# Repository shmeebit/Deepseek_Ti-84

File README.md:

# DeepSeek-TI-84  (calculator ↔ AI)
A TI-84 Plus CE Python asks DeepSeek-R1 questions over a $7 ESP32-S3 dongle.

Note: WIP clean-up — use these files while we finish repairs
- ESP32-S3 firmware: esp32s3/esp32s3_host_clean.ino
- TI-84 program: ti84/ti32_ai_clean.py
The original files showed merge artifacts; the clean versions above are known-good starting points.

## 1. What you need to buy (exact parts)
| Qty | Part | Footprint | Mouser | LCSC | Notes |
|----:|------|-----------|--------|------|-------|
| 1   | XIAO ESP32-S3 | dev-board | 356-ESP32S3XIAO | C558488 | already has USB-C |
| 1   | USB-C receptacle 6-pin mid-mount | - | 798-006-0101-1 | C134092 | board edge |
| 2   | 5.1 kΩ 0603 | 0603 | - | C23187 | CC1/CC2 pull-downs |
| 2   | 100 nF 0603 | 0603 | - | C14663 | decoupling |
| 1   | PCB | 50 × 25 mm | order gerber.zip below | JLCJLCJLC | $4 for 5 pcs |

Total ≈ US $7 + PCB.

## 2. Order the PCB (2 min)
1. Download [pcb/gerber.zip](pcb/gerber.zip)  
2. Upload to [jlcpcb.com](https://jlcpcb.com), 2-layer, 1 mm, black, 1 oz Cu.  
3. Quantity 5, shipping as you like → ≈ $4 delivered.

## 3. Flash the ESP32-S3 (30 s)
```bash
# Linux/macOS/WSL
python flash_firmware.py   # auto-downloads UF2, puts XIAO in DFU, flashes

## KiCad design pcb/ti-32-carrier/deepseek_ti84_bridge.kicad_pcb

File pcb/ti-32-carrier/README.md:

# KiCad Starter Project: TI-32 Carrier

Open `ti-32-carrier.kicad_pro` in KiCad 8. This starter includes:
- A blank but annotated schematic sheet with block notes and nets reference
- An empty board with a 60 x 35 mm outline (Edge.Cuts) and a title

Recommended next steps
1. Place symbols (or replace with your part choices):
   - Connector: `Connector:USB_A` (or use `Connector:USB_C_Receptacle_USB2.0` + CC pull-ups)
   - ESD: `Power_Protection:USBLC6-2SC6`
   - Switch: `Power_Switch:AP2331` (or `TPS2553`) – if missing, use a generic `Regulator_Switch` symbol and update later
   - Boost: `Regulator_Switching` family (e.g., `MT3608` or `TPS61023` symbol from community libs) – you can start with a generic boost symbol
   - Battery: `Connector_Generic:Conn_01x02` for JST-PH
   - XIAO: use two 1x7/1x8 headers to represent the module pins or add a custom symbol later
2. Label nets:
   - `BAT`, `+5V`, `VBUS`, `D+`, `D-`, `EN_VBUS`
   - Tie `EN_VBUS` to XIAO pin `GPIO10 (D16)` by net label
3. Run ERC, then Assign Footprints:
   - USB-A receptacle footprint (vertical or right-angle)
   - ESD diode SOT-23-6
   - AP2331 SOT-23-5 (or TPS2553 MSOP-8/SON)
   - Boost (MT3608 SOT-23-6 or your chosen IC)
   - JST-PH-2 for battery
4. Update PCB from schematic and place parts:
   - Keep D+/D- short, matched, away from the boost loop
   - ESD next to the connector
   - Switch close to connector; 10–22 µF bulk cap on VBUS
   - Observe XIAO antenna keep-out near the USB end of the module

Notes
- The firmware defaults EN_VBUS to GPIO10 (D16). If you pick another pin, update `PIN_VBUS_EN` in `esp32s3/esp32s3_host.ino`.
- For USB-C, add 5.1 kΩ `Rp` on CC1/CC2 to +5V to advertise a 5V source.

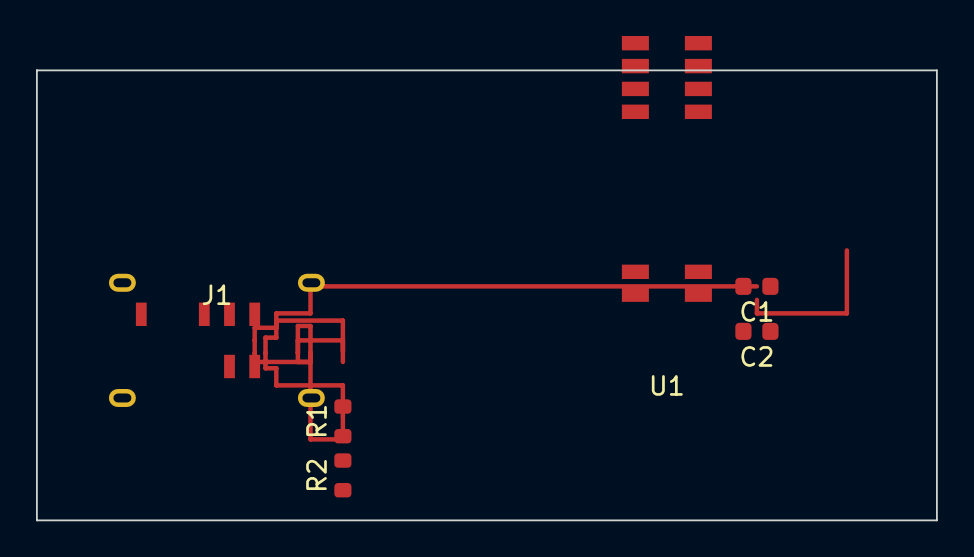
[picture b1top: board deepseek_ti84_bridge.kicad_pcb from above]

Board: 2 copper layers, 50.0 x 25.0 mm, 6 parts (0 on the bottom side), 7 nets.

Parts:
C1, C2: 100 nF; C_0603_1608Metric
J1: USB_C; USB_C_Receptacle_HRO_TYPE-C-31-M-12
R1, R2: 5.1 kΩ; R_0603_1608Metric
U1: XIAO_ESP32-S3; Seeed_XIAO_ESP32-S3

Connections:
3V3: C1.1, U1.1, U1.12
CC1: J1.A6, R1.1
CC2: J1.B6, R2.1
D+: J1.A7, U1.2, U1.11
D-: J1.B7, U1.3, U1.10
GND: C1.2, C2.2, J1.A1, R1.2, R2.2, U1.4, U1.5, U1.7, U1.8, U1.9
VBUS: C2.1, J1.A4, U1.6

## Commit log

2025-10-22 "Innitial commit"
2025-10-22 Complete TI-32 implementation: ESP32 firmware, TI-84 programs, and documentation
    - Implemented TI link protocol (get_str/set_str) with USB bulk transfers
    - Added interface claiming and endpoint discovery in ESP32 firmware
    - Created command loop for polling calculator and processing AI queries
    - Built ti32_ai.py: full-featured calculator program with menu system
    - Added simple_test.py: minimal test program for quick verification
    - Comprehensive documentation: QUICKSTART.md and ti84/README.md
2025-10-22 Optimize for Seeed Studio XIAO ESP32S3
    - Add comprehensive XIAO_ESP32S3_GUIDE.md with setup instructions
    - Update firmware comments to clarify XIAO requirements
    - Add Arduino IDE configuration steps for XIAO board
    - Include XIAO-specific pinout reference (GPIO10/D16 for VBUS)
    - Update PCB guide to highlight XIAO form factor
    - Clarify VBUS power requirement (external circuit needed)
2025-10-24 Fix critical implementation issues
    - Complete server dependencies in package.json
    - Add comprehensive environment configuration
    - Implement proper ESP32-S3 USB host with TI link protocol
    - Fix TI-84 Python programs with proper ti_system usage
    - Add detailed hardware setup documentation
    Fixes #1: USB host implementation incomplete
2025-10-24 Update to fix (Hopefully) critical issues
2025-10-24 Add photo placeholder in hardware setup
    Add photo placeholder in hardware setup
2025-10-25 repo hygiene: one README, exact BOM, tidy folders, tiny PCB
2025-10-25 Add Flask and Requests to requirements.txt
2025-10-25 Add clean ESP32-S3 firmware (esp32s3_host_clean.ino) and clean TI-84 app (ti32_ai_clean.py); original files appear corrupted.
2025-10-25 Docs: point to clean firmware/app; gitignore KiCad caches/backups
2025-10-25 cleanup
